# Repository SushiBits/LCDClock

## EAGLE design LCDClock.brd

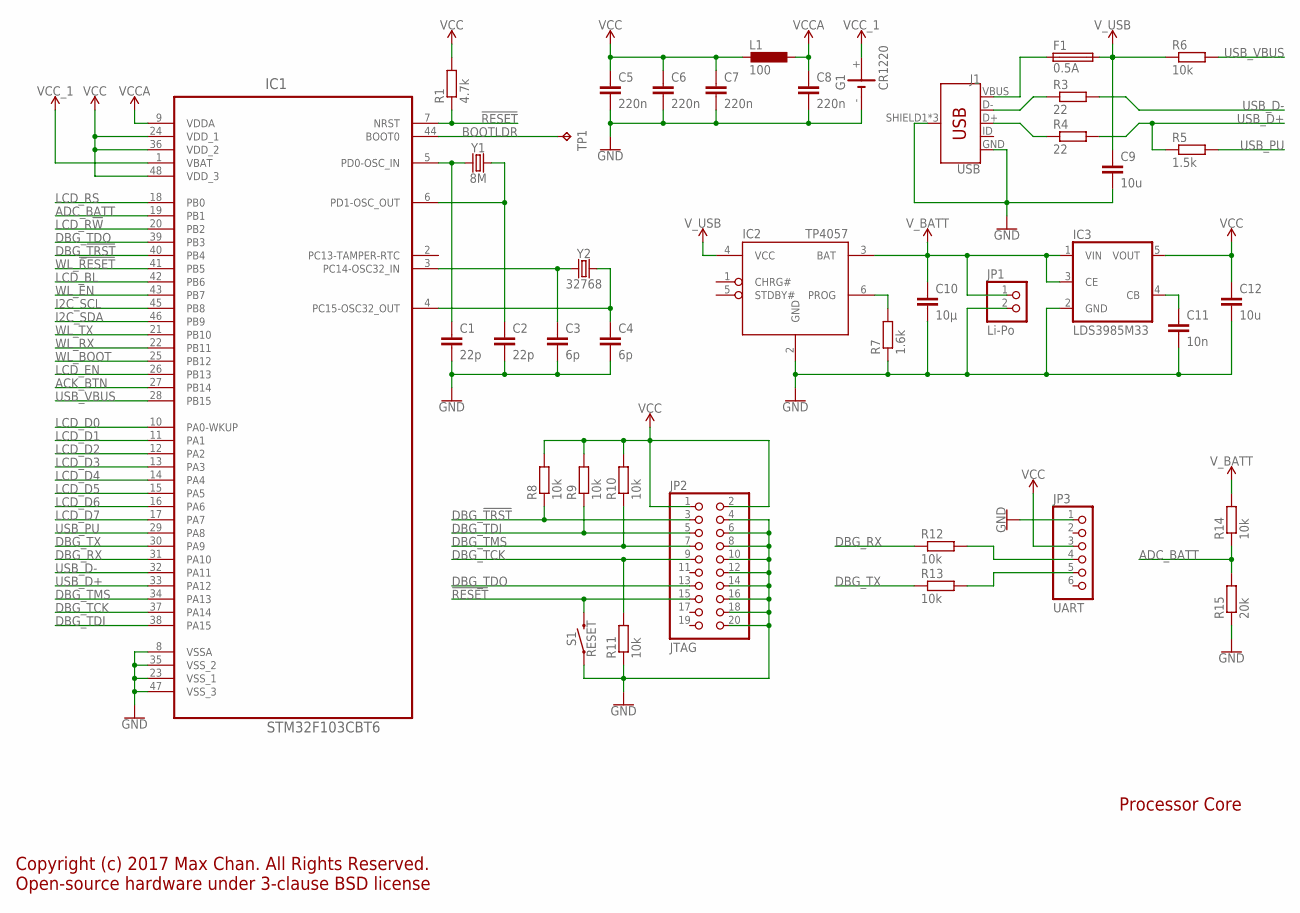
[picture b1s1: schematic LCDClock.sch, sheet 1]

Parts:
C1, C2: 22p; C0603
C3, C4: 6p; C0603
C5, C6, C7, C8: 220n; C0603
C9, C12: 10u; C0805
C10: 10µ; C0805
C11: 10n; C0603
F1: 0.5A; R1206
G1: CR1220; CH291-1220LF
IC1: STM32F103CBT6; QFP50P900X900X160-48N
IC2: TP4057; SOT23-6
IC3: LDS3985M33; SOT25
J1: USB; USB-B-MICRO-SMD
JP1: Li-Po; 1X02
JP2: JTAG; 2X10/90
JP3: UART; 1X06/90
L1: 100; L2012C
R1: 4.7k; R0603
R3, R4: 22; R0603
R5: 1.5k; R0603
R6, R8, R9, R10, R11, R12, R13, R14: 10k; R0603
R7: 1.6k; R0603
R15: 20k; R0603
S1: RESET; TACTILE_SWITCH_SMD_6.0X3.5MM
TP1: TPTP10R; TP10R
Y1: 8M; CRYSTAL-SMD-5X3.2-4PAD
Y2: 32768; CRYSTAL-SMD-3.2X1.5MM

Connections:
!RESET: IC1.7 (NRST), JP2.15, R1.1, S1.2
ACK_BTN: IC1.27 (PB14); also elsewhere on the board
ADC_BATT: IC1.19 (PB1), R14.1, R15.2
BATT_PROG: IC2.6 (PROG), R7.2
BOOTLDR: IC1.44 (BOOT0), TP1.TP
DBGRX: JP3.4, R12.2
DBGTX: JP3.5, R13.2
DBG_!TRST: IC1.40 (PB4), JP2.3, R8.1
DBG_RX: IC1.31 (PA10), R12.1
DBG_TCK: IC1.37 (PA14), JP2.9, R11.2
DBG_TDI: IC1.38 (PA15), JP2.5, R9.1
DBG_TDO: IC1.39 (PB3), JP2.13
DBG_TMS: IC1.34 (PA13), JP2.7, R10.1
DBG_TX: IC1.30 (PA9), R13.1
GND: C1.2, C2.2, C3.2, C4.2, C5.2, C6.2, C7.2, C8.2, C9.2, C10.2, C11.2, C12.2, G1.-, IC1.8 (VSSA), IC1.23 (VSS_1), IC1.35 (VSS_2), IC1.47 (VSS_3), IC2.2 (GND), IC3.2 (GND), J1.GND, J1.SHIELD1 (SHIELD), J1.SHIELD2 (SHIELD), J1.SHIELD3 (SHIELD), JP1.2, JP2.4, JP2.6, JP2.8, JP2.10, JP2.12, JP2.14, JP2.16, JP2.18, JP2.20, JP3.1, R7.1, R11.1, R15.1, S1.1; also elsewhere on the board
HSE_IN: C1.1, IC1.5 (PD0-OSC_IN), Y1.1
HSE_OUT: C2.1, IC1.6 (PD1-OSC_OUT), Y1.3 (2)
I2C_SCL: IC1.45 (PB8); also elsewhere on the board
I2C_SDA: IC1.46 (PB9); also elsewhere on the board
LCD_BL: IC1.42 (PB6); also elsewhere on the board
LCD_D0: IC1.10 (PA0-WKUP); also elsewhere on the board
LCD_D1: IC1.11 (PA1); also elsewhere on the board
LCD_D2: IC1.12 (PA2); also elsewhere on the board
LCD_D3: IC1.13 (PA3); also elsewhere on the board
LCD_D4: IC1.14 (PA4); also elsewhere on the board
LCD_D5: IC1.15 (PA5); also elsewhere on the board
LCD_D6: IC1.16 (PA6); also elsewhere on the board
LCD_D7: IC1.17 (PA7); also elsewhere on the board
LCD_EN: IC1.26 (PB13); also elsewhere on the board
LCD_R!W: IC1.20 (PB2); also elsewhere on the board
LCD_RS: IC1.18 (PB0); also elsewhere on the board
LSE_IN: C3.1, IC1.3 (PC14-OSC32_IN), Y2.P$1 (1)
LSE_OUT: C4.1, IC1.4 (PC15-OSC32_OUT), Y2.P$2 (2)
UD+: J1.D+, R4.1
UD-: J1.D-, R3.1
USB_D+: IC1.33 (PA12), R4.2, R5.1
USB_D-: IC1.32 (PA11), R3.2
USB_PU: IC1.29 (PA8), R5.2
USB_VBUS: IC1.28 (PB15), R6.2
VBUS: F1.1, J1.VBUS
VCC: C5.1, C6.1, C7.1, C12.1, IC1.24 (VDD_1), IC1.36 (VDD_2), IC1.48 (VDD_3), IC3.5 (VOUT), JP2.1, JP2.2, JP3.3, L1.2, R1.2, R8.2, R9.2, R10.2; also elsewhere on the board
VCCA: C8.1, IC1.9 (VDDA), L1.1
VCC_1: G1.+, IC1.1 (VBAT)
VCC_FILT: C11.1, IC3.4 (CB)
V_BATT: C10.1, IC2.3 (BAT), IC3.1 (VIN), IC3.3 (CE), JP1.1, R14.2; also elsewhere on the board
V_USB: C9.1, F1.2, IC2.4 (VCC), R6.1
WL_!RESET: IC1.41 (PB5); also elsewhere on the board
WL_BOOT: IC1.25 (PB12); also elsewhere on the board
WL_EN: IC1.43 (PB7); also elsewhere on the board
WL_RX: IC1.22 (PB11); also elsewhere on the board
WL_TX: IC1.21 (PB10); also elsewhere on the board

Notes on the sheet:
Copyright (c) 2017 Max Chan. All Rights Reserved. Open-source hardware under 3-clause BSD license
Processor Core

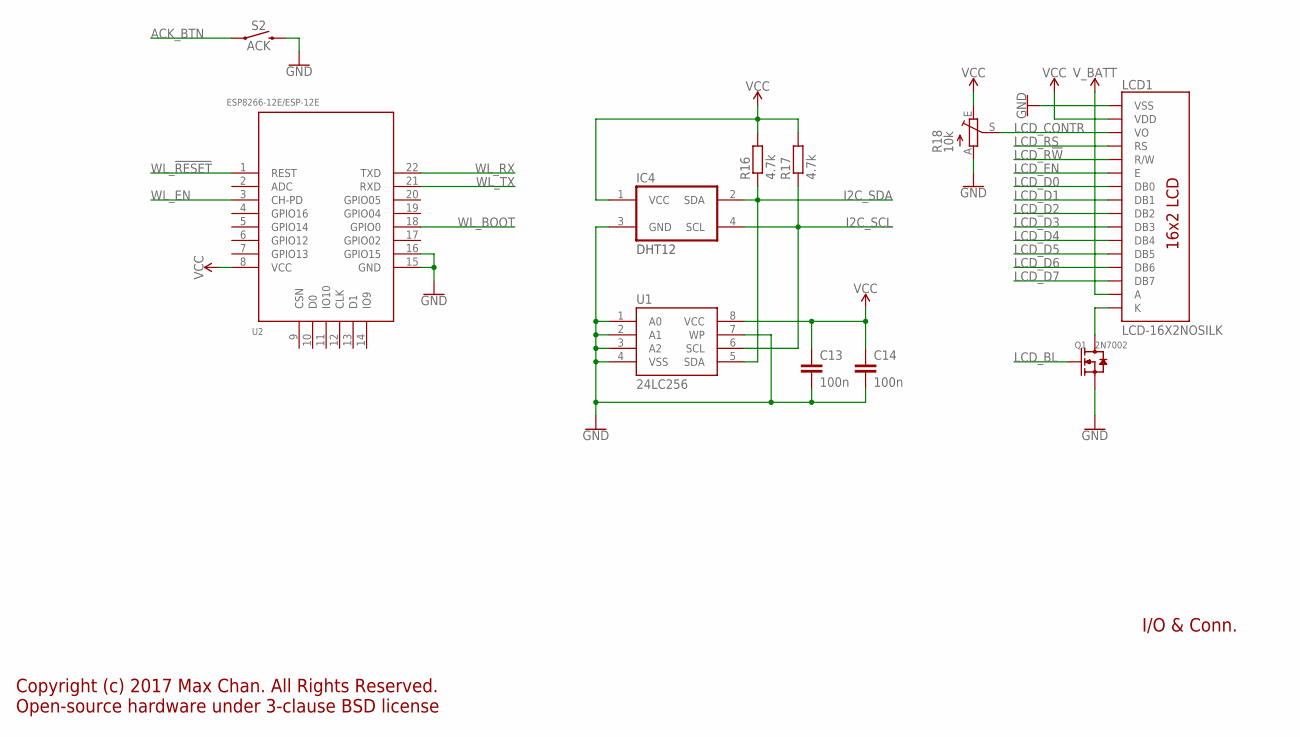
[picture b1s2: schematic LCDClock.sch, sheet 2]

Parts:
C13, C14: 100n; C0603
IC4: DHT12
LCD1: LCD-16X2NOSILK; LCD-16X2_NOSILK
Q1: 2N7002; SOT-23
R16, R17: 4.7k; R0603
R18: 10k; CA6V
S2: ACK; TACTILE_SWITCH_PTH_RIGHT_ANGLE_KIT
U1: 24LC256; SO08
U2: ESP8266-12E/ESP-12E; LGA22-2.0-24X16MM

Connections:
ACK_BTN: S2.1; also elsewhere on the board
GND: C13.2, C14.2, IC4.3 (GND), LCD1.1 (VSS), Q1.2 (S), R18.A, S2.2, U1.1 (A0), U1.2 (A1), U1.3 (A2), U1.4 (VSS), U1.7 (WP), U2.15 (GND), U2.16 (GPIO15); also elsewhere on the board
I2C_SCL: IC4.4 (SCL), R17.1, U1.6 (SCL); also elsewhere on the board
I2C_SDA: IC4.2 (SDA), R16.1, U1.5 (SDA); also elsewhere on the board
LCDBL: LCD1.16 (K), Q1.3 (D)
LCD_BL: Q1.1 (G); also elsewhere on the board
LCD_CONTR: LCD1.3 (VO), R18.S
LCD_D0: LCD1.7 (DB0); also elsewhere on the board
LCD_D1: LCD1.8 (DB1); also elsewhere on the board
LCD_D2: LCD1.9 (DB2); also elsewhere on the board
LCD_D3: LCD1.10 (DB3); also elsewhere on the board
LCD_D4: LCD1.11 (DB4); also elsewhere on the board
LCD_D5: LCD1.12 (DB5); also elsewhere on the board
LCD_D6: LCD1.13 (DB6); also elsewhere on the board
LCD_D7: LCD1.14 (DB7); also elsewhere on the board
LCD_EN: LCD1.6 (E); also elsewhere on the board
LCD_R!W: LCD1.5 (R/W); also elsewhere on the board
LCD_RS: LCD1.4 (RS); also elsewhere on the board
VCC: C13.1, C14.1, IC4.1 (VCC), LCD1.2 (VDD), R16.2, R17.2, R18.E, U1.8 (VCC), U2.8 (VCC); also elsewhere on the board
V_BATT: LCD1.15 (A); also elsewhere on the board
WL_!RESET: U2.1 (REST); also elsewhere on the board
WL_BOOT: U2.18 (GPIO0); also elsewhere on the board
WL_EN: U2.3 (CH-PD); also elsewhere on the board
WL_RX: U2.22 (TXD); also elsewhere on the board
WL_TX: U2.21 (RXD); also elsewhere on the board

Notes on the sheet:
Copyright (c) 2017 Max Chan. All Rights Reserved. Open-source hardware under 3-clause BSD license
I/O & Conn.

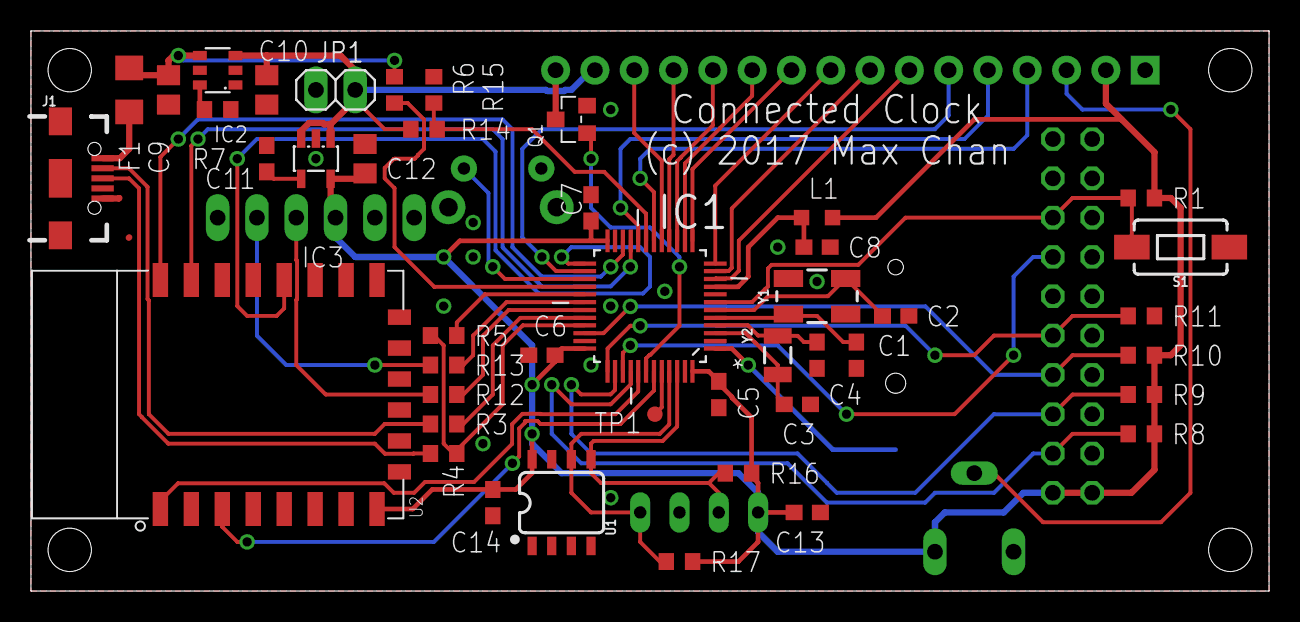
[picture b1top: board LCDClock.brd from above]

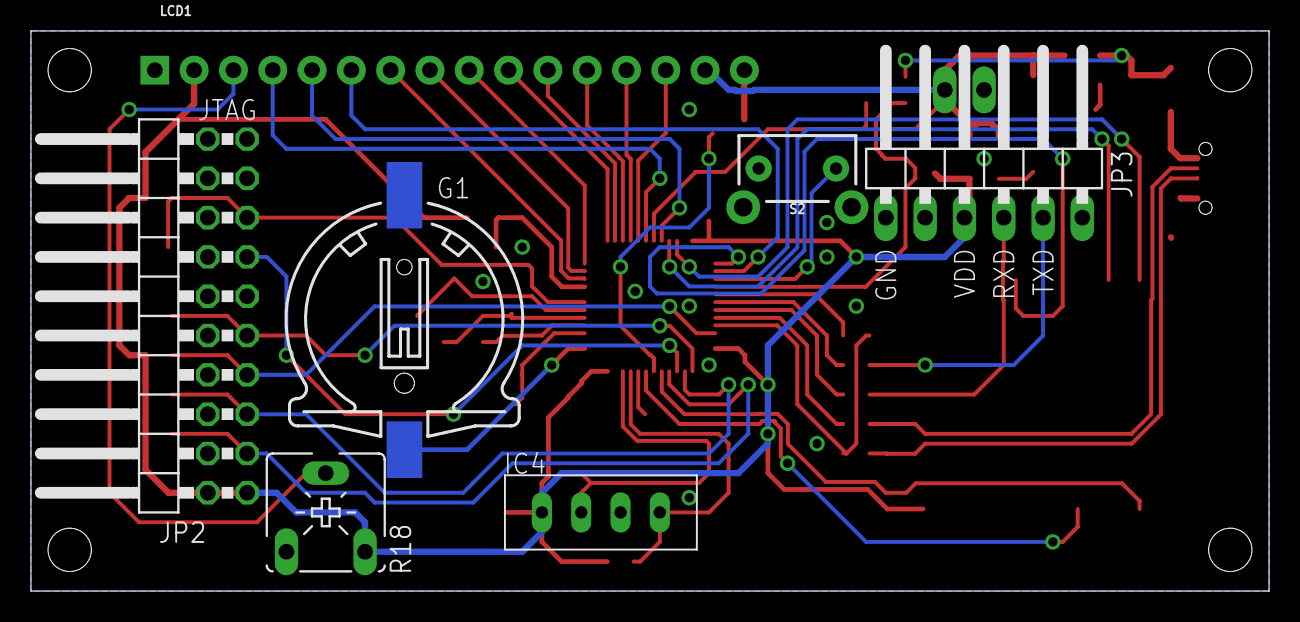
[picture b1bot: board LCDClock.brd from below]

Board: 2 copper layers, 80.0 x 36.2 mm, 51 parts (7 on the bottom side), 53 nets.

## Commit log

2017-08-21 Initial

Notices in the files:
parts and their libraries:
SparkFun-Connectors: Licensing: Creative Commons ShareAlike 4.0 International - https://creativecommons.org/licenses/by-sa/4.0
